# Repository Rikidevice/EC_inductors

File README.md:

# PWR_MOD — контроллер индуктивного измерения проводимости солей с регулировкой pH
# PWR_MOD — Inductive Salt Conductivity Meter with pH Control

[Русский](#русская-версия) · [English](#english-version)

---

## Русская версия

Плата управления для системы индуктивного (бесконтактного) измерения
проводимости солей трендового типа с автоматической коррекцией pH.
Поддерживает два варианта управляющего модуля: **ESP32 / ESP32-S3-1.47**
и **STM32F407VET6**. Связь по **Modbus (RTU/ASCII)**.

### Возможности

- **Индуктивный метод измерения проводимости солей**
  - Приём сигнала с катушки детекции (Rx) через **полноценный АЦП**
    с **гальванической развязкой**.
  - Отдельный канал измерения **pH** (также через развязанный АЦП).
- **Температурный контроль**
  - **DS18B20** — температура жидкости (1-Wire).
  - **DHT22 (AM2302)** — температура и влажность воздуха в помещении.
- **Управляющие модули (на выбор / распайка под оба):**
  - `ESP32` (WROOM-32 и совместимые);
  - `ESP32-S3-1.47` (дисплейный модуль);
  - `STM32F407VET6`.
- **Два шаговых двигателя** для дозирования:
  - `pH Up` — драйвер A4988;
  - `pH Down` — драйвер A4988.
- **Modbus**
- **Питание и защита** — 12В от 1А

### Аппаратная часть

| Узел | Реализация | Примечание |
|---|---|---|
| MCU | ESP32 / ESP32-S3-1.47 / STM32F407VET6 | выбор при сборке |
| АЦП (Rx катушки) | MCP3551 | гальваническая развязка |
| АЦП (pH) | ADS1232 | гальваническая развязка |
| Датчик температуры жидкости | DS18B20 | 1-Wire |
| Датчик температуры/влажности воздуха | DHT22 (AM2302) | 1-Wire-подобный |
| Драйвер ШД №1 (pH Up) | A4988 | полноценная обвязка |
| Драйвер ШД №2 (pH Down) | A4988 | полноценная обвязка |
| Интерфейс связи | Modbus RTU / ASCII | RS-485 - SN65HVD72DR |

**Плата:** 4 слоя, 111,1-91,3 мм.

### Прошивка и протокол

- **Modbus:** [RTU / ASCII], адрес по умолчанию — `[1]`,
  скорость — `[9600 8N1 / 19200 8N1]`.
- **Карта регистров:** [ссылка на docs/modbus_registers.md или таблицу ниже].

#### Карта регистров (черновик)

| Адрес | R/W | Описание | Ед. |
|---|---|---|---|
| 0x0000 | R | Проводимость солей | мкСм/см |
| 0x0001 | R | pH | pH |
| 0x0002 | R | Температура жидкости (DS18B20) | °C |
| 0x0003 | R | Температура воздуха (DHT22) | °C |
| 0x0004 | R | Влажность воздуха (DHT22) | % |
| 0x0010 | W | Уставка pH | pH |
| 0x0011 | W | Команда насоса pH Up | — |
| 0x0012 | W | Команда насоса pH Down | — |
| 0x00FF | R/W | Служебный / версия ПО | — |

### Сборка и запуск

1. Подать питание 12В (есть защита от полярности).
2. Проверить индикацию [PWR, RUN].
3. Подключить сборку из катушек Tx [L2], Rx [L3].
4. Подключить pH-электрод к разъёму [J5].
5. Подключить DS18B20 к разъёму [18b20].
6. Подключить DHT22 к разъёму [DHT22].
7. Подключить RS-485 (A/B/GND) [J11]  к верхнему уровню.
8. Подать команду по Modbus и убедиться в отклике.

### Безопасность

- Измерительная и цифровая части разделены по земле и питанию.
- Шаговые двигатели питаются от входного напряжения 12В

### Лицензия

Проект распространяется под лицензией **MIT**. Полный текст — в файле [`LICENSE`](LICENSE).

### Автор

[Talgat / RikiDevice] — [rikimtfree@gmail.com]

---

## English version

Control board for an inductive (non-contact) salt conductivity measurement
system of trending type with automatic pH correction.
Supports two control module options: **ESP32 / ESP32-S3-1.47**
and **STM32F407VET6**. Communication over **Modbus (RTU/ASCII)**.

### Features

- **Inductive salt conductivity measurement**
  - Detection coil (Rx) signal acquisition via a **full-featured ADC**
    with **galvanic isolation**.
  - Dedicated **pH** measurement channel (also via isolated ADC).
- **Temperature monitoring**
  - **DS18B20** — liquid temperature (1-Wire).
  - **DHT22 (AM2302)** — ambient air temperature and humidity.
- **Control modules (selectable / footprint for both):**
  - `ESP32` (WROOM-32 and compatible);
  - `ESP32-S3-1.47` (display module);
  - `STM32F407VET6`.
- **Two stepper motors** for dosing:
  - `pH Up` — A4988 driver;
  - `pH Down` — A4988 driver.
- **Modbus** — communication with upper layer (PLC / SCADA / PC).
- **Power and protection** — [specify: input voltage, regulators,
  overcurrent protection, TVS, etc.].

### Hardware

| Block | Implementation | Notes |
|---|---|---|
| MCU | ESP32 / ESP32-S3-1.47 / STM32F407VET6 | selected at build time |
| ADC (Rx coil) | [part] | galvanically isolated |
| ADC (pH) | [part] | galvanically isolated |
| Liquid temperature sensor | DS18B20 | 1-Wire, [parasitic/external power] |
| Ambient temp/humidity sensor | DHT22 (AM2302) | 1-Wire-like, [4.7–10 kΩ pull-up] |
| Stepper driver #1 (pH Up) | A4988 | full support circuitry |
| Stepper driver #2 (pH Down) | A4988 | full support circuitry |
| Communication | Modbus RTU / ASCII | RS-485 [transceiver] |
| Power | [voltage] | [regulators / protections] |

**PCB:** 4 layers, [size, mm], [thickness, mm], [accuracy class].

### Repository layout
PWR_MOD/
├─ PWR_MOD.kicad_pro # KiCad project
├─ PWR_MOD.kicad_sch # schematic
├─ PWR_MOD.kicad_pcb # PCB layout
├─ gerbers/ # Gerber + drill files
├─ docs/ # datasheets, PDFs, notes
│ ├─ schematic.pdf
│ ├─ pcb_top.pdf
│ └─ pcb_bottom.pdf
├─ firmware/ # firmware sources (if any)
├─ .gitignore
└─ README.md
text

### Fabrication

1. Open the project in **KiCad [version]**.
2. Run ERC (schematic) and DRC (PCB) — report saved to `docs/`.
3. Generate Gerber + Excellon (drill) into `gerbers/`.
4. Send `gerbers/*.zip` to the PCB house.
   - Layers: 4 (Top, Inner1, Inner2, Bottom).
   - [Optional] controlled impedance if required for the detection coil.

### Firmware and protocol

- **Modbus:** [RTU / ASCII], default address — `[1]`,
  default baud — `[9600 8N1 / 19200 8N1]`.
- **Register map:** [link to docs/modbus_registers.md or table below].

#### Register map (draft)

| Address | R/W | Description | Unit |
|---|---|---|---|
| 0x0000 | R | Salt conductivity | µS/cm |
| 0x0001 | R | pH | pH |
| 0x0002 | R | Liquid temperature (DS18B20) | °C |
| 0x0003 | R | Ambient temperature (DHT22) | °C |
| 0x0004 | R | Ambient humidity (DHT22) | % |
| 0x0010 | W | pH setpoint | pH |
| 0x0011 | W | pH Up pump command | — |
| 0x0012 | W | pH Down pump command | — |
| 0x00FF | R/W | Service / firmware version | — |

### Assembly and startup

1. Apply power [voltage, polarity].
2. Check indicators [PWR, RUN, ERR].
3. Connect the Rx coil to connector [J?].
4. Connect the pH electrode to connector [J?].
5. Connect DS18B20 to connector [J?].
6. Connect DHT22 to connector [J?].
7. Connect RS-485 (A/B/GND) to the upper layer.
8. Send a Modbus command and verify the response.

### Safety

- Galvanic isolation of the ADC is mandatory: measurement and digital
  sections are separated by ground and power.
- Stepper motors are powered from a separate [voltage] rail and **must not**
  share ground with the isolated ADC.
- When handling pH reagents (Up/Down), observe [safety precautions].

### License

The project is distributed under the MIT license. The full text is in the [`LICENSE`](LICENSE).

### Author

[Talgat / RikiDevice] — [rikimtfree@gmail.com]

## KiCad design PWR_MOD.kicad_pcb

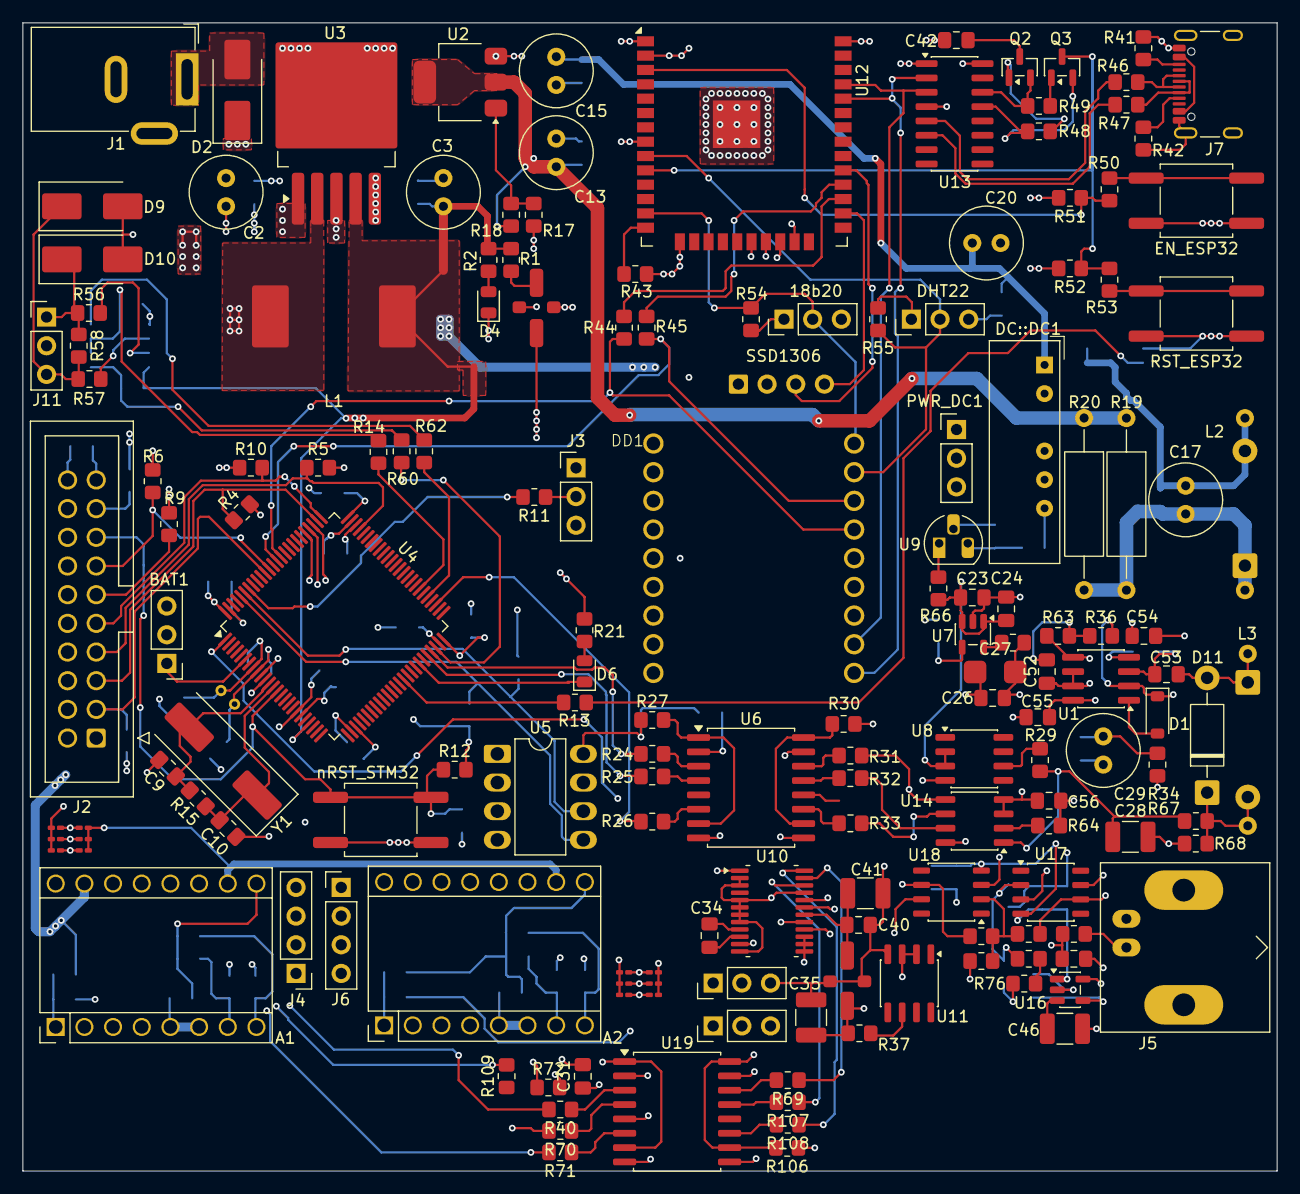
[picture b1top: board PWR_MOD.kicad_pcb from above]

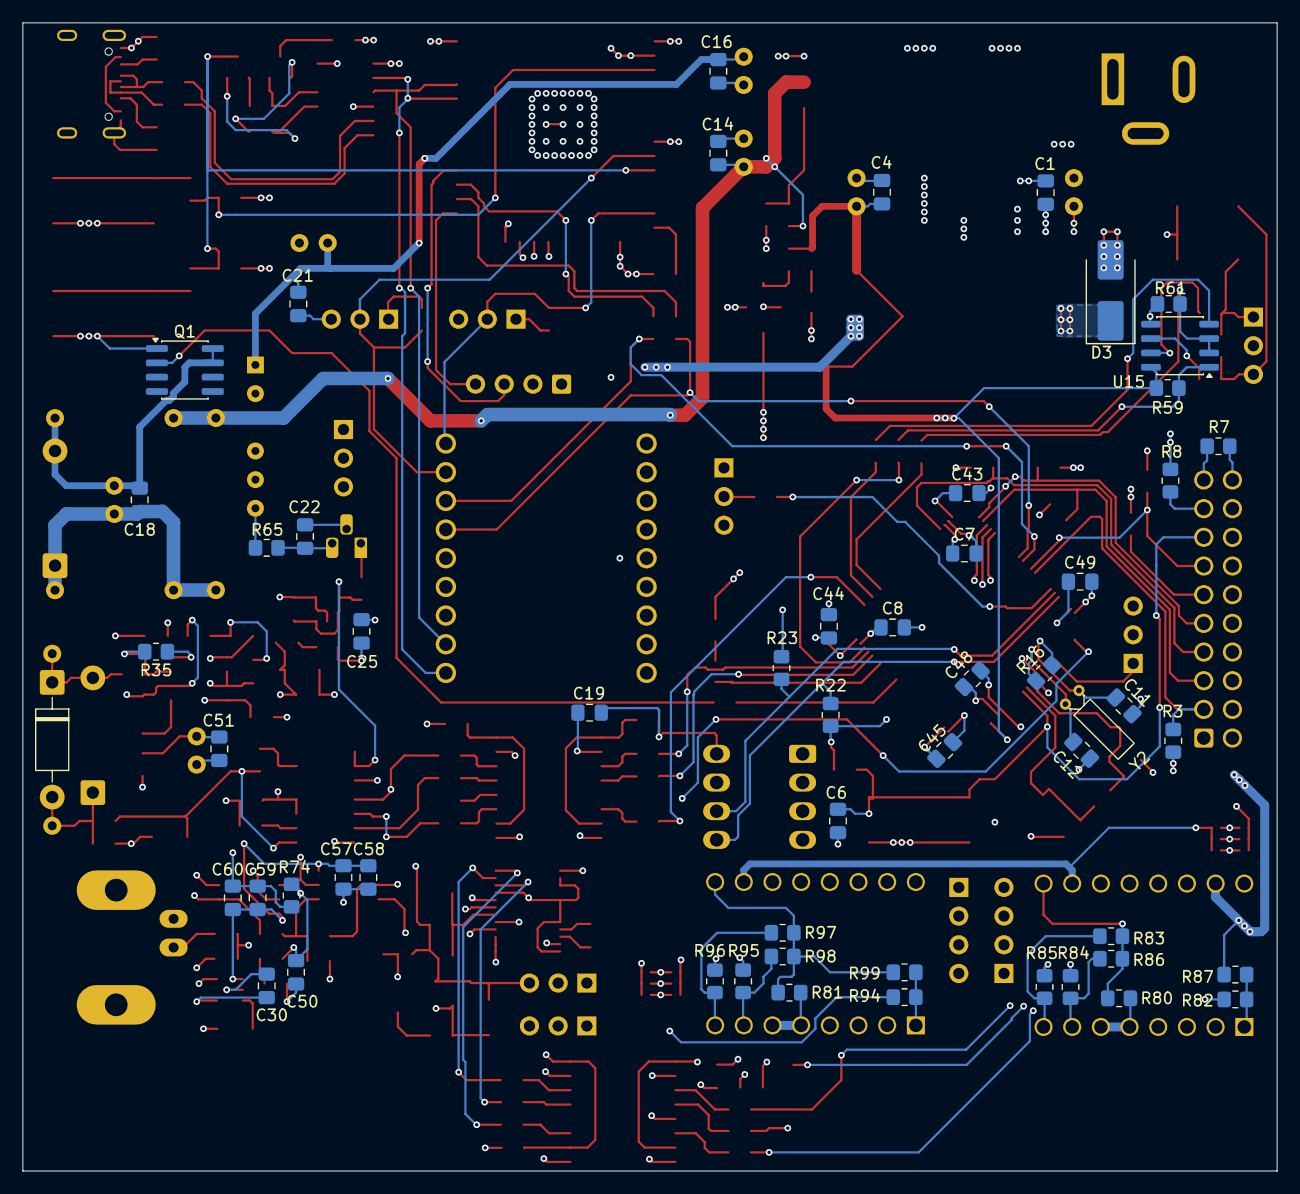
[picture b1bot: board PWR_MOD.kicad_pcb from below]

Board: 4 copper layers, 111.1 x 101.7 mm, 221 parts (57 on the bottom side), 164 nets.

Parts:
18b20: Conn_01x03; PinHeader_1x03_P2.54mm_Vertical
A1, A2: Pololu_Breakout_A4988; Pololu_Breakout-16_15.2x20.3mm
BAT1: Conn_01x03; PinHeader_1x03_P2.54mm_Vertical
C1, C4, C14, C16, C18, C21, C22, C23, C25: C_Small; C_0805_2012Metric_Pad1.18x1.45mm_HandSolder
C2, C3, C13, C15, C17, C20: C_Polarized_Small; C_Radial_D6.3mm_H7.0mm_P2.50mm
C5, C39: C_Feedthrough; L_0805_2012Metric_Pad1.05x1.20mm_HandSolder
C6, C7, C8, C19, C31, C43, C44, C45, C48, C49: 0.1 uF; C_0805_2012Metric_Pad1.18x1.45mm_HandSolder
C9, C10, C11, C12: 10 pF; C_0805_2012Metric_Pad1.18x1.45mm_HandSolder
C24: 0,1 uF; C_0805_2012Metric_Pad1.18x1.45mm_HandSolder
C26, C27, C40, C51: 6800; C_0805_2012Metric_Pad1.18x1.45mm_HandSolder
C28, C35, C46: 10 uF; C_1210_3225Metric_Pad1.33x2.70mm_HandSolder
C29: 220 uF; C_Radial_D6.3mm_H7.0mm_P2.50mm
C30: 100n; C_0805_2012Metric_Pad1.18x1.45mm_HandSolder
C34, C42: 1 uF; C_0805_2012Metric_Pad1.18x1.45mm_HandSolder
C41: 47 uF; C_1210_3225Metric_Pad1.33x2.70mm_HandSolder
C47: 2.2n; C_0805_2012Metric_Pad1.18x1.45mm_HandSolder
C50, C57, C58, C59, C60: 1u; C_0805_2012Metric_Pad1.18x1.45mm_HandSolder
C52: 21 old 150; C_0805_2012Metric_Pad1.18x1.45mm_HandSolder
C53, C55: 1500; C_0805_2012Metric_Pad1.18x1.45mm_HandSolder
C54: 51 old 330; C_0805_2012Metric_Pad1.18x1.45mm_HandSolder
C56: ???; C_0805_2012Metric_Pad1.18x1.45mm_HandSolder
D1: MBR0540; D_SOD-123
D2, D3, D9, D10: SS24; D_SMB_Handsoldering
D4, D6: LED; LED_0805_2012Metric
D5, D8, D11: 1N4007; D_DO-41_SOD81_P10.16mm_Horizontal
DC::DC1: Converter_DCDC_Murata_NMAxxxxSC_THT
DD1: Без имени
DHT22: Conn_01x03; PinHeader_1x03_P2.54mm_Vertical
EN_ESP32: boot; SW_Push_1P1T_NO_CK_KSC6xxG
GAIN1, GAIN2: Conn_01x03; PinHeader_1x03_P2.54mm_Vertical
J1: Barrel_Jack; BarrelJack_GCT_DCJ200-10-A_Horizontal
J2: Conn_ARM_JTAG_SWD_20; IDC-Header_2x10_P2.54mm_Vertical
J3, J11: Conn_01x03; PinHeader_1x03_P2.54mm_Vertical
J4, J6: Conn_01x04_Pin; PinHeader_1x04_P2.54mm_Vertical
J5: Conn_Coaxial; BNC_Amphenol_B6252HB-NPP3G-50_Horizontal
J7: USB_C_Receptacle_USB2.0_16P; USB_C_Receptacle_GCT_USB4105-xx-A_16P_TopMnt_Horizontal
L1: L; L_Changjiang_FXL1340
L2: Tx; R_Axial_DIN0309_L9.0mm_D3.2mm_P15.24mm_Horizontal
L3: Rx; R_Axial_DIN0309_L9.0mm_D3.2mm_P15.24mm_Horizontal
PWR_DC1: Conn_01x03; PinHeader_1x03_P2.54mm_Vertical
Q1: IRF7341PBF; SOIC-8_3.9x4.9mm_P1.27mm
Q2, Q3: SS8050; SOT-23
R1, R28, R29, R37, R65, R66: 0; R_0805_2012Metric_Pad1.20x1.40mm_HandSolder
R2, R24, R25, R26, R31, R32, R33, R40, R69, R70, R71, R74, R107, R108, R109: 1k; R_0805_2012Metric_Pad1.20x1.40mm_HandSolder
R3, R4, R5, R6, R7, R8, R9, R10, R35, R43, R51, R52, R59, R61, R67, R68: 10k; R_0805_2012Metric_Pad1.20x1.40mm_HandSolder
R11, R12, R17, R21: 3.3k; R_0805_2012Metric_Pad1.20x1.40mm_HandSolder
R13, R14, R27, R30, R50, R53, R72, R106: 100; R_0805_2012Metric_Pad1.20x1.40mm_HandSolder
R15, R16: 1M; R_0805_2012Metric_Pad1.20x1.40mm_HandSolder
R18: 560; R_0805_2012Metric_Pad1.20x1.40mm_HandSolder
R19, R20: R; R_Axial_DIN0309_L9.0mm_D3.2mm_P15.24mm_Horizontal
R22, R23, R80, R81, R83, R86, R87, R97, R98, R99: 4.7k; R_0805_2012Metric_Pad1.20x1.40mm_HandSolder
R34: 100k; R_0805_2012Metric_Pad1.20x1.40mm_HandSolder
R36, R63: 3.6k; R_0805_2012Metric_Pad1.20x1.40mm_HandSolder
R41, R42: 5.1k; R_0805_2012Metric_Pad1.20x1.40mm_HandSolder
R44, R45, R46, R47, R56, R57, R60, R62, R64: 10; R_0805_2012Metric_Pad1.20x1.40mm_HandSolder
R48, R49: 12k; R_0805_2012Metric_Pad1.20x1.40mm_HandSolder
R54, R55: 4,7k; R_0805_2012Metric_Pad1.20x1.40mm_HandSolder
R58: 120; R_0805_2012Metric_Pad1.20x1.40mm_HandSolder
R73: 4.7M; R_0805_2012Metric_Pad1.20x1.40mm_HandSolder
R75: 1-5k*; R_0805_2012Metric_Pad1.20x1.40mm_HandSolder
R76: 2.2k; R_0805_2012Metric_Pad1.20x1.40mm_HandSolder
R77, R78: 30k; R_0805_2012Metric_Pad1.20x1.40mm_HandSolder
R79: 75k; R_0805_2012Metric_Pad1.20x1.40mm_HandSolder
R82, R84, R85, R94, R95, R96: 220; R_0805_2012Metric_Pad1.20x1.40mm_HandSolder
R88, R89, R90, R91, R92, R93, R100, R101, R102, R103, R104, R105: 4.7k; R_0201_0603Metric_Pad0.64x0.40mm_HandSolder
RST_ESP32: SW_Push; SW_Push_1P1T_NO_CK_KSC6xxG
SSD1306: ER_OLEDM0.91_1x-I2C
U1: AD8606ARZ; SOIC-8_3.9x4.9mm_P1.27mm
U2: LM317_SOT-223; SOT-223-3_TabPin2
U3: LM2576S-ADJ; TO-263-5_TabPin3
U4: STM32F407VETx; LQFP-100_14x14mm_P0.5mm
U5: 24LC256; DIP-8_W7.62mm_LongPads
U6, U19: ADuM1401xRW; SOIC-16W_7.5x10.3mm_P1.27mm
U7: LP2985-3.3; SOT-23-5
U8, U11: REF195; SO-8_3.9x4.9mm_P1.27mm
U9: L7809; TO-92L_HandSolder
U10: ADS1232IPW; HTSSOP-24-1EP_4.4x7.8mm_P0.65mm_EP3.4x7.8mm_Mask2.4x4.68mm
U12: ESP32-WROOM-32
U13: CH340C; SOIC-16_3.9x9.9mm_P1.27mm
U14: MCP3551-EMS; SO-8_3.9x4.9mm_P1.27mm
U15: SO-8_3.9x4.9mm_P1.27mm
U16: TPS60400DBV; SOT-23-5
U17: CA3140; JEITA_SOIC-8_3.9x4.9mm_P1.27mm
U18: TL081; JEITA_SOIC-8_3.9x4.9mm_P1.27mm
Y1: 8 MHz; Crystal_SMD_HC49-SD
Y2: 32k; Crystal_DS15_D1.5mm_L5.0mm_Horizontal
nRST_STM32: SW_Push; SW_Push_1P1T_NO_CK_KSC6xxG

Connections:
+3.3 VDD: C5.3, C19.1, C31.1, C43.2, C44.2, C45.2, C48.2, C49.2, J2.1 (VTREF), J2.2 (VCC/NC), J3.1, R3.2, R4.2, R5.2, R6.2, R12.2, R21.2, R22.1, R23.1, R27.1, R72.1, U4.11 (VDD), U4.19 (VDD), U4.28 (VDD), U4.50 (VDD), U4.75 (VDD), U4.100 (VDD), U5.8 (VCC)
+3.3 VDDA: 18b20.1, A1.10 (VDD), A2.10 (VDD), C3.1, C4.1, DD1.3V3, DHT22.1, L1.2, R1.1, R2.1, R51.2, R52.2, R54.2, R55.2, R59.1, R91.1, R92.1, R93.1, R100.1, R101.1, R102.1, SSD1306.2 (VCC), U3.4 (FB), U4.22 (VDDA), U12.2 (VDD), U13.4 (V3), U13.16 (VCC), U15.8 (VCC)
+3.3V1: C26.1, C27.1, C55.2, GAIN1.1, GAIN2.1, R28.2, R30.1, R106.1, U1.8 (V+), U10.1 (DVDD), U14.8 (Vdd)
+9: C13.1, C14.1, R18.1, R19.1, R20.1, U2.2 (VO)
+9V1: C23.1, C24.1, PWR_DC1.2, R66.1, U7.1 (VIN), U7.3 (ON/~OFF), U8.2 (Vin), U8.3 (~Sleep), U11.2 (Vin), U11.3 (~Sleep)
+OUT DC: C22.1, PWR_DC1.3, R65.1, U9.3 (IN)
+V: A1.16 (VMOT), A2.16 (VMOT), C1.1, C2.1, C15.1, C16.1, C20.1, C21.1, D2.1 (K), DC::DC1.1 (+Vin), U2.3 (VI), U3.1 (VIN)
+VIN: D2.2 (A), J1.1
+Vin_ADC: R64.1, U14.2 (Vin+)
+Vref: C28.1, R29.2, R67.1, U14.1 (Vref)
+Vref_1232: C30.1, C35.1, C39.1, R37.2, U10.16 (REFP), U16.2 (IN), U17.7 (V+), U18.7 (V+)
-Vin_ADC: C22.2, C23.2, C24.2, C25.2, C26.2, C27.2, C28.2, C29.2, C30.2, C35.2, C39.2, C40.2, C41.2, C47.1, C51.2, C54.1, C55.1, C56.1, C57.1, C58.1, C59.1, C60.1, DC::DC1.4 (-Vout), GAIN1.3, GAIN2.3, J5.2 (Ext), PWR_DC1.1, R34.1, R35.1, R68.1, R74.1, U1.4 (V-), U6.9 (GND2), U6.15 (GND2), U7.2 (GND), U8.4 (GND), U9.2 (GND), U10.2 (DGND), U10.3 (CLKIN/XTAL1), U10.5 (DGND), U10.6 (DGND), U10.7 (TEMP), U10.8 (A0), U10.12 (AINN1), U10.13 (AINN2), U10.14 (AINP2), U10.15 (REFN), U10.17 (AGND), U10.21 (SPEED), U11.4 (GND), U14.3 (Vin-), U14.4 (Vss), U16.4 (GND), U18.3 (+), U19.9 (GND2), U19.15 (GND2)
-Vref: C57.2, C58.2, C59.2, C60.2, R79.1, U16.1 (OUT), U17.4 (V-), U18.4 (V-)
AinP1: R78.2, U10.11 (AINP1), U18.6
BOOT0: R11.2, U4.94 (BOOT0)
CS: R25.2, U4.46 (PE15)
CS_1: R32.1, U14.7 (~CS)
CS_1232: R107.1, U10.22 (~PWDN)
CS_ADS1232: R70.2, U4.1 (PE2)
D+: J7.A6 (D+), J7.B6 (D+), R46.1
D-: J7.A7 (D-), J7.B7 (D-), R47.1
DIR: DD1.2, R85.1, R96.1, U12.21 (SDO/SD0)
DOUT_ADS1232: R108.1, U10.24 (~DRDY/DOUT)
DTR: Q3.2 (E), R48.1, U13.13 (~DTR)
EN: R50.2, R51.1, U12.3 (EN)
G0: GAIN1.2, U10.19 (GAIN0)
G1: GAIN2.2, U10.20 (GAIN1)
GND_0: 18b20.3, A1.9 (GND), A1.15 (GND), A2.9 (GND), A2.15 (GND), BAT1.2, BAT1.3, C1.2, C2.2, C3.2, C4.2, C5.2, C6.2, C7.2, C8.2, C9.2, C10.2, C11.2, C12.2, C13.2, C14.2, C15.2, C16.2, C19.2, C20.2, C21.2, C31.2, C42.2, C43.1, C44.1, C45.1, C48.1, C49.1, D3.2 (A), D4.1 (K), D9.2 (A), D10.2 (A), DC::DC1.2 (-Vin), DD1.GND, DHT22.3, EN_ESP32.2, J1.2, J2.4 (GND), J2.6 (GND), J2.8 (GND), J2.10 (GND), J2.12 (GND), J2.14 (GND), J2.16 (GND), J2.18 (GND), J2.20 (GND), J3.3, J7.A1 (GND), J7.A12 (GND), J7.B1 (GND), J7.B12 (GND), J7.SH (SHIELD), J11.2, Q1.1 (S1), R7.1, R8.1, R9.1, R10.1, R17.1, R41.2, R42.2, R43.2, R61.2, R80.1, R81.1, R83.1, R86.1, R87.1, R88.1, R89.1, R90.1, R97.1, R98.1, R99.1, R103.1, R104.1, R105.1, RST_ESP32.2, SSD1306.1 (GND), U3.3 (GND), U3.5 (~ON/OFF), U4.10 (VSS), U4.20 (VSSA), U4.27 (VSS), U4.74 (VSS), U4.99 (VSS), U5.1 (A0), U5.2 (A1), U5.3 (A2), U5.4 (GND), U5.7 (WP), U6.2 (GND1), U6.5 (VIC), U6.8 (GND1), U12.1 (GND), U12.8 (IO32), U12.15 (GND), U12.38 (GND), U12.39 (GND), U13.1 (GND), U15.5 (GND), U19.2 (GND1), U19.5 (VIC), U19.8 (GND1), nRST_STM32.2
IIC_SCL: SSD1306.3 (SCL), U12.29 (IO5)
IIC_SDA: SSD1306.4 (SDA), U12.26 (IO4)
IO0: Q3.3 (C), R52.1, R53.2, U12.10 (IO25)
JTCK: J2.9 (TCK/SWCLK), R10.2, U4.76 (SYS_JTCK-SWCLK)
JTDI: J2.5 (TDI), R4.1, U4.77 (SYS_JTDI)
JTDO: J2.13 (TDO/SWO), R6.1, U4.89 (SYS_JTDO-SWO)
JTMS: J2.7 (TMS/SWDIO), R5.1, U4.72 (SYS_JTMS-SWDIO)
LC_Tx: Q1.2 (G1), R13.2
LED_TEST: D6.1 (K), U4.44 (PE13)
M1: DD1.3, R82.1, U12.22 (SDI/SD1)
M2: DD1.4, R94.1, U12.23 (IO15)
MISO_AD1232: R71.2, U4.79 (PC11)
MOSI_AD1232: R109.2, U4.80 (PC12)
unnamed: A1.12 (1A), J4.3
unnamed: A1.11 (1B), J4.4
unnamed: A1.13 (2A), J4.2
unnamed: A1.14 (2B), J4.1
unnamed: A1.8 (DIR), R83.2, R85.2
unnamed: A1.2 (MS1), R90.2, R91.2
unnamed: A1.3 (MS2), R89.2, R92.2
unnamed: A1.4 (MS3), R88.2, R93.2
unnamed: A1.7 (STEP), R84.2, R86.2
unnamed: A1.1 (~ENABLE), R82.2, R87.2
unnamed: A1.5 (~RESET), A1.6 (~SLEEP), R80.2
unnamed: A2.12 (1A), J6.3
unnamed: A2.11 (1B), J6.4
unnamed: A2.13 (2A), J6.2
unnamed: A2.14 (2B), J6.1
unnamed: A2.8 (DIR), R96.2, R97.2
unnamed: A2.2 (MS1), R100.2, R103.2
unnamed: A2.3 (MS2), R101.2, R104.2
unnamed: A2.4 (MS3), R102.2, R105.2
unnamed: A2.7 (STEP), R95.2, R98.2
unnamed: A2.1 (~ENABLE), R94.2, R99.2
unnamed: A2.5 (~RESET), A2.6 (~SLEEP), R81.2
unnamed: C5.1, R1.2
unnamed: C34.1, U10.9 (CAP)
unnamed: C34.2, U10.10 (CAP)
unnamed: C50.2, R76.2, R77.1, U17.6
unnamed: C52.1, R36.1, R63.2
unnamed: D1.2 (A), U1.1
unnamed: C29.1, C51.1, D1.1 (K), R34.2, R36.2, U1.2 (-)
unnamed: D3.1 (K), L1.1, U3.2 (OUT)
unnamed: D4.2 (A), R2.2
unnamed: C17.2, C18.2, D5.2 (A), L2.2, Q1.7 (D1), Q1.8 (D1)
unnamed: C17.1, C18.1, D5.1 (K), L2.1, R19.2, R20.2
unnamed: D6.2 (A), R21.1
unnamed: D9.1 (K), J11.3, R57.1, R58.2
unnamed: D10.1 (K), J11.1, R56.1, R58.1
unnamed: C53.1, D8.1 (K), D11.2 (A), L3.2
unnamed: D8.2 (A), D11.1 (K), L3.1, R67.2, R68.2
unnamed: DC::DC1.6 (+Vout), R65.2
unnamed: EN_ESP32.1, R50.1
unnamed: J2.19 (DBGACK/NC), R7.2
unnamed: J2.17 (DBGRQ/NC), R8.2
unnamed: J2.11 (RTCK), R9.2
unnamed: J3.2, R11.1
unnamed: J5.1 (In), R73.1
unnamed: J7.A5 (CC1), R42.1
unnamed: J7.B5 (CC2), R41.1
unnamed: J7.A4 (VBUS), J7.A9 (VBUS), J7.B4 (VBUS), J7.B9 (VBUS)
unnamed: Q2.1 (B), R48.2
unnamed: C42.1, Q2.3 (C)
unnamed: Q3.1 (B), R49.2
unnamed: R53.1, RST_ESP32.1
unnamed: R75.2, R76.1
unnamed: C53.2, R35.2, U1.3 (+)
unnamed: C54.2, R63.1, U1.5 (+)
unnamed: C52.2, C56.2, R64.2, U1.6 (-), U1.7
unnamed: R17.2, R18.2, U2.1 (ADJ)
unnamed: R14.1, U4.57 (PD10)
unnamed: R13.1, U4.40 (PE9)
unnamed: R27.2, U6.1 (VDD1), U6.7 (VE1)
unnamed: R30.2, U6.10 (VE2), U6.16 (VDD2)
unnamed: R24.1, U6.3 (VIA)
unnamed: R25.1, U6.4 (VIB)
unnamed: R33.2, U6.11 (VID)
unnamed: R31.2, U6.14 (VOA)
unnamed: R32.2, U6.13 (VOB)
unnamed: R26.1, U6.6 (VOD)
unnamed: C25.1, U7.4 (BP)
unnamed: R28.1, U7.5 (VOUT)
unnamed: R29.1, U8.6 (Vout)
unnamed: R66.2, U9.1 (OUT)
unnamed: C39.3, C40.1, C41.1, U10.18 (AVDD)
unnamed: R37.1, U11.6 (Vout)
unnamed: R43.1, U12.14 (IO12)
unnamed: R44.1, U12.27 (IO16)
unnamed: R45.1, U12.28 (IO17)
unnamed: R46.2, U13.5 (UD+)
unnamed: R47.2, U13.6 (UD-)
unnamed: R57.2, U15.6 (A)
unnamed: R56.2, U15.7 (B)
unnamed: R62.1, U15.4 (DI)
unnamed: R59.2, R60.1, U15.1 (RO)
unnamed: C46.1, U16.5 (C_{FLY+})
unnamed: C46.2, U16.3 (C_{FLY-})
unnamed: C47.2, R73.2, U17.3 (+)
unnamed: C50.1, R74.2, R75.1, U17.2 (-)
unnamed: R77.2, R78.1, R79.2, U18.2 (-)
unnamed: R72.2, U19.1 (VDD1), U19.7 (VE1)
unnamed: R106.2, U19.10 (VE2), U19.16 (VDD2)
unnamed: R40.1, U19.3 (VIA)
unnamed: R70.1, U19.4 (VIB)
unnamed: R108.2, U19.11 (VID)
unnamed: R69.2, U19.14 (VOA)
unnamed: R107.2, U19.13 (VOB)
unnamed: R71.1, U19.6 (VOD)
OSC32_IN: C11.1, R16.2, U4.8 (RCC_OSC32_IN), Y2.2
OSC32_OUT: C12.1, R16.1, U4.9 (RCC_OSC32_OUT), Y2.1
OSC_IN: C9.1, R15.2, U4.12 (RCC_OSC_IN), Y1.2
OSC_OUT: C10.1, R15.1, U4.13 (RCC_OSC_OUT), Y1.1
OneWire 18b20: 18b20.2, DD1.7, R54.1, U12.13 (IO14)
OneWire DHT11: DD1.8, DHT22.2, R55.1, U12.9 (IO33)
RTS: Q2.2 (E), R49.1, U13.14 (~RTS)
SCK: R24.2, U4.47 (PB10)
SCK_1: R31.1, U14.5 (SCK)
SCK_STM32_AD1232: R40.2, U4.78 (PC10)
SCLK_ADS1232: R69.1, U10.23 (SCLK)
SCL_I2C1: R23.2, U4.95 (PB8), U5.6 (SCL)
SDA_I2C1: R22.2, U4.96 (PB9), U5.5 (SDA)
SDO: R26.2, U4.53 (PB14)
SDO_1: R33.1, U14.6 (SDO/~RDY)
STP: DD1.0, R84.1, R95.1, U12.20 (SCK/CLK)
U0R: DD1.TXD, U12.34 (RXD0/IO3), U13.2 (TXD)
U0T: DD1.RXD, U12.35 (TXD0/IO1), U13.3 (RXD)
U2RxD: DD1.10, R44.2, U4.86 (PD5)
U2TxD: DD1.9, R45.2, U4.87 (PD6)
U3CK: R14.2, R61.1, U15.2 (RE), U15.3 (DE)
U3RxD: R60.2, U4.48 (PB11)
U3TxD: R62.2, U4.55 (PD8)
VBAT: BAT1.1, U4.6 (VBAT)
VCAP2: C7.1, U4.73 (VCAP_2)
VCAP_1: C8.1, U4.49 (VCAP_1)
nRST: C6.1, J2.15 (~SRST), R12.1, U4.14 (NRST), nRST_STM32.1
nTRST: J2.3 (~TRST), R3.1, U4.90 (SYS_JTRST)

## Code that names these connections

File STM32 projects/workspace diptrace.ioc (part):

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Mcu.Name=STM32F407V(E-G)Tx
Mcu.Package=LQFP100
Mcu.UserName=STM32F407VETx
PA1.Signal=ADCx_IN1
PA13.Mode=JTAG_5_pins
PA13.Signal=SYS_JTMS-SWDIO
PA14.Mode=JTAG_5_pins
PA14.Signal=SYS_JTCK-SWCLK
PA15.Mode=JTAG_5_pins
PA15.Signal=SYS_JTDI
PA2.Signal=ADCx_IN2
PA3.Signal=ADCx_IN3
PA4.Signal=GPXTI4
PA5.Signal=ADCx_IN5
PB10.GPIOParameters=GPIO_PuPd
PB10.GPIO_PuPd=GPIO_PULLDOWN
PB10.Mode=Full_Duplex_Master
PB10.Signal=SPI2_SCK
PB11.Mode=Synchronous
PB11.Signal=USART3_RX
PB12.Signal=GPIO_Output
PB13.GPIOParameters=GPIO_Speed,GPIO_PuPd
PB13.GPIO_PuPd=GPIO_PULLUP
PB13.GPIO_Speed=GPIO_SPEED_FREQ_MEDIUM
PB13.Signal=GPIO_Output
PB14.GPIOParameters=GPIO_PuPd
PB14.GPIO_PuPd=GPIO_PULLUP
PB14.Mode=Full_Duplex_Master
PB14.Signal=SPI2_MISO
PB15.GPIOParameters=GPIO_PuPd
PB15.GPIO_PuPd=GPIO_PULLDOWN
PB15.Mode=Full_Duplex_Master
PB15.Signal=SPI2_MOSI
PB3.Mode=JTAG_5_pins
PB3.Signal=SYS_JTDO-SWO
PB4.Mode=JTAG_5_pins
PB4.Signal=SYS_JTRST
PB8.Mode=I2C
PB8.Signal=I2C1_SCL
PB9.Mode=I2C
PB9.Signal=I2C1_SDA
PC10.GPIOParameters=GPIO_PuPd
PC10.GPIO_PuPd=GPIO_PULLDOWN
PC10.Mode=Full_Duplex_Master
PC10.Signal=SPI3_SCK
PC11.GPIOParameters=GPIO_PuPd
PC11.GPIO_PuPd=GPIO_PULLUP
PC11.Mode=Full_Duplex_Master
PC11.Signal=SPI3_MISO
PC12.GPIOParameters=GPIO_PuPd
PC12.GPIO_PuPd=GPIO_PULLDOWN
PC12.Mode=Full_Duplex_Master
PC12.Signal=SPI3_MOSI
PC14-OSC32_IN.Mode=LSE-External-Oscillator
PC14-OSC32_IN.Signal=RCC_OSC32_IN
PC15-OSC32_OUT.Mode=LSE-External-Oscillator
PC15-OSC32_OUT.Signal=RCC_OSC32_OUT
PD10.Mode=Synchronous
PD10.Signal=USART3_CK
PD5.Mode=Asynchronous
PD5.Signal=USART2_TX
PD6.Mode=Asynchronous
PD6.Signal=USART2_RX
PD8.Mode=Synchronous
PD8.Signal=USART3_TX
PE11.Signal=S_TIM1_CH2
PE13.Signal=GPIO_Output
PE15.GPIOParameters=GPIO_PuPd
PE15.GPIO_PuPd=GPIO_PULLUP
PE15.Signal=GPIO_Output
PE2.Signal=GPIO_Output
PE9.GPIOParameters=GPIO_Speed,GPIO_PuPd
PE9.GPIO_PuPd=GPIO_PULLDOWN
PE9.GPIO_Speed=GPIO_SPEED_FREQ_MEDIUM
PE9.Signal=S_TIM1_CH1
PH0-OSC_IN.Mode=HSE-External-Oscillator
PH0-OSC_IN.Signal=RCC_OSC_IN
PH1-OSC_OUT.Mode=HSE-External-Oscillator
PH1-OSC_OUT.Signal=RCC_OSC_OUT
RCC.HSE_VALUE=20000000
RCC.SYSCLKFreq_VALUE=168000000
RCC.SYSCLKSource=RCC_SYSCLKSOURCE_PLLCLK
board=custom
